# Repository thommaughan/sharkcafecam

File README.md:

# sharkcafecam
SharkCafe Cam - white shark camera tag with behavior detection triggered video

### How to navigate this repository
First of all, welcome to Shark Cafe Camera. The first thing that you will need to review is the "ToolList.md" file. This will provide you with the necessary tools and optional tools that will assist you with completing this project. Each tool is listed as the name of the tool, cost, and a blue hyperlink text which will take you the the website to order that tool. Tools that are listed as optional are not necessary for the project but can provide some ease with certain aspects. The tools listed as none optional were chosen as ideal due to the fact that you can go to your local hardware store and purchase these tools and they are the relatively cheaper versions. These are not the specific tools we used for this project but are merely recommendations. Feel free to find, borrow, or use other tools that will accomplish the same tasks.

The next step if you are not familiar with soldering should be to review the "SolderingBasics.md". This will provide you a brief overview of soldering tools and techniques that will assist you with this project. Feel free to also research other resources for example you tube videos or manuals as these can provide more detailed information about this topic.

After you have completed the first two sections or you are familiar with soldering then you are ready to navigation the rest of this repository. The organization of this reprository is as follows. Each folder describes a certain component of the overall project. The subfolders within each of these folders has  a combination of subfolder including a readme.md, mechanical, electrical, and software. First, you should open the "readme.md" which provides necessary information or steps for that component. The Mechanical describes any physical component or mechanism for that component. The electrical describes the components used and how the were wired. The software describes any software that was used to control the electrical components. 

Use these materials as guidelines to further experiment with other cameras or devices. This is merely to show how this project was accomplished and the potential possibilities. 

If you have any questions or any part of these materials are confusion, please feel free to leave comments on sections that are confusing. 

Have fun and go exploring with your new remote sensing camera!

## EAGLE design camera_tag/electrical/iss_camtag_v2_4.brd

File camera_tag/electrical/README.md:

# Shark Cafe Cam Main Board Information
## Files
#### 1. Schematic
#### 2. Board design
## Internal components

#### 1. Processor
#### 2. Sensors  
   Note: We show breakout boards for the sensors to show that these can be bought seperately, utilized individually, and have code and tutrials available by their manufacturers online. On the board these sensors are cut down to the essentials to make for a more compact design.
#### 3. Camera trigger
```
Note on camera trigger transistors: they allow for switching the camera on/off and record/stop. These transistors work by allowing current to flow through the camera when they are triggered. In a way they act as an electrical switch, when power is sent to them you're flipping the switch 'on', thus activating the camera, when no power is sent, the switch is flipped 'off' and the camera disactivates.
```

### Processor

| Part         | Function          | Board Code    | Description       | Link and part number      |
| --------------------|:-------------:|:-------------:|-----------------|----------------- |
|  | Processor | N/A | Central processing. Same processor found in Feather M0, can be accessed as such through Arduino IDE.| ATSAMD21G18A |

### Sensors (included)

| Part breakout board         | Function          | Board Code    | Description       | Link and part number      |
| --------------------|:-------------:|:-------------:|-----------------|:---------------------------:|
|   | RGB sensor  | U1  | Red, green, blue light sensor  |  [ISL29125](https://www.sparkfun.com/products/12829)   |
|   | IMU        | U4           | Accelerometer, gyroscope, and compass | [MPU-9250](https://www.invensense.com/products/motion-tracking/9-axis/mpu-9250/)   |
|   | Capacitive sensing         |   U6   | 4 Channel Capacitance to Digital Converter  | [FDC1004](http://www.ti.com/product/FDC1004)  |

### Trigger (for camera or other device. Transistor.)

| Location on board         | Function          | Board Code    | Description       | Link and part number      |
| --------------------|:-------------:| -------------|-----------------|---------------------------|
|   |  2 FETs, one turns the camera on/off and the other records/stops.  | CAM1  | Trigger for camera. R and P are transistor drains, G is the common source.  |  [Transistors](https://learn.sparkfun.com/tutorials/transistors/all#extending-the-water-analogy)   |

### Electrical components

| Part Number/Name         | Function          | Board Code    | Description       | Link       |
|:--------------------:|:-------------:|:-------------:|:-----------------:|:-----------------:|
| SN74LVC2G66DCUR  | Switch         | U5    | Dual Bilateral Analog Switch  | [SN74LVC2G66DCUR](http://www.ti.com/lit/ds/symlink/sn74lvc2g66.pdf)  |
| TPS22918            | Load Switch         | U8     | Details in datasheet  | [TPS22918](http://www.ti.com/product/TPS22918)  |
| 2N7002BKS           | MOSFET         | Q1     | Transistor drain  | [2N7002BKS](https://assets.nexperia.com/documents/data-sheet/2N7002BKS.pdf)  |
| ZXCT1109            | Current sense monitor         |   U9   | Details in datasheet  | [ZXCT1109](https://www.diodes.com/assets/Datasheets/ZXCT1107_10.pdf)  |
| TPS78033            | LDO regulator         | U7     | Details in datasheet  | [TPS78033](https://www.findchips.com/detail/tps78033/2477-Texas%20Instruments?quantity=1)  |
| MCP73831            | Charge Management controller         |  U3    | Details in datasheet  | [MCP73831](https://cdn.sparkfun.com/assets/learn_tutorials/6/9/5/MCP738312.pdf)  |
| Direct wire uSD connect        | Micro SD card connector         |   J9   | Pins for soldering MicroSD card on.  | N/A  |
| USB-MICROB 5v                | Data transfer and power with computer         | J6     | Micro USB connector port  | N/A  |
   
 ### *For information on how to communicate with the board and each sensor, check out the software section.*

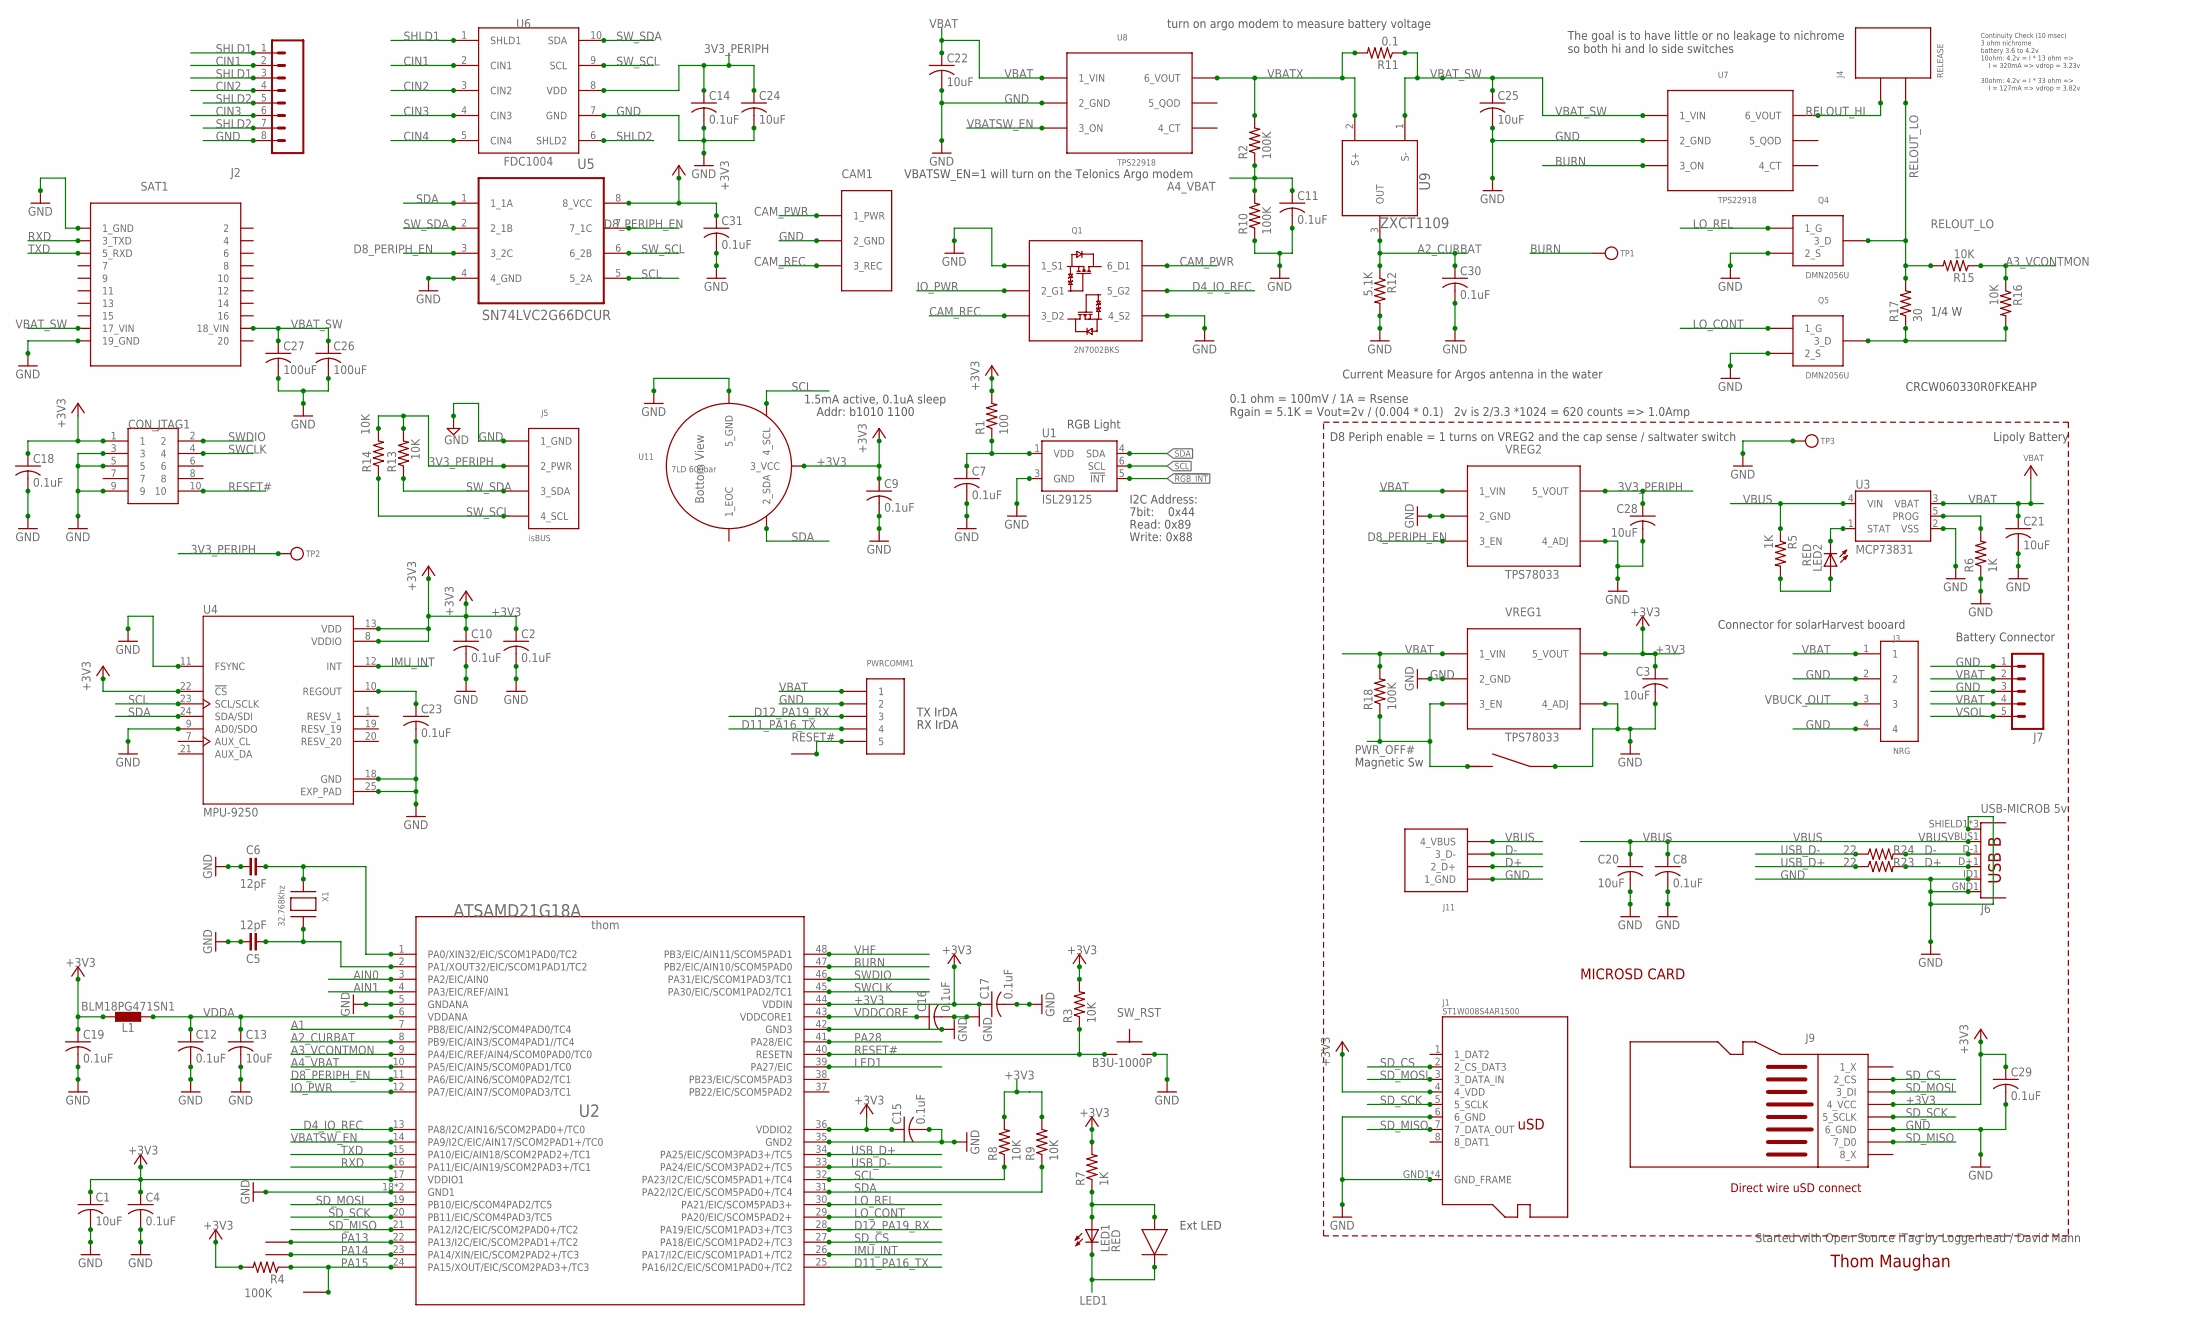
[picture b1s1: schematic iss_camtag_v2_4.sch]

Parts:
C1, C13, C20, C21, C22, C24, C25: 10uF; C0603
C2, C4, C7, C8, C9, C10, C11, C12, C14, C15, C16, C17, C18, C19, C23, C29, C30, C31: 0.1uF; C0402
C3, C28: 10uF; C0603K
C5, C6: 12pF; C0402
C26, C27: 100uF; C1210
CAM1: CON_1X3_CAMCTRL
CON_JTAG1: HDR-SMT-50MIL/5X2
J1: ST1W008S4AR1500; MICROSD_JAE_ST1W008S4AR1500
J2: CONN_08"; 1X08
J3: NRG; CONNECTOR_1X4_0_1
J4: RELEASE; CON_1X2_0_1
J5: isBUS; CON_1X4_0_1
J6: USB-MICROB 5v; USB-B-MICRO-SMD_V03
J7: M05PTH; 1X05
J9: CON_8_MICROSD_WIRE
J11: CON_1X4_2MM_THRU
L1: BLM18PG471SN1; C0603
LED1, LED2: RED; CHIPLED_0603
PWRCOMM1: CON_1X5_0_1; CONNECTOR_1X5_0_1
Q1: 2N7002BKS; SOT363
Q4, Q5: DMN2056U; SOT23-3
R1: 100; R0402
R2, R4, R10, R18: 100K; R0402
R3, R8, R9, R13, R14, R15, R16: 10K; R0402
R5, R6, R7: 1K; R0402
R11: 0.1; R0603
R12: 5.1K; R0402
R17: 30; R0603
R23, R24: 22; R0402
SAT1: TELONICS-ST-21H2-200A; TELONICS_ST_21H2-200A
SW_RST: B3U-1000P
TP1, TP2, TP3: TESTPOINTROUND1.5MM; TESTPOINT_ROUND_1.5MM
TP4, TP5, TP6: CON_1
U1: ISL29125; ODFN-LD-6
U2: ATSAMD21G18A; TQFN48_7MM
U3: MCP73831; SOT23-5
U4: MPU-9250; MPU-9250-FOOTPRINT
U5: SN74LVC2G66DCUR; ANALOG_SW_SN74LVCG66DCUR
U6: FDC1004; VSSOP-10
U7, U8: TPS22918; SOT23-6
U9: ZXCT1109; SOT23
U11: 7LD 600bar; KELLER_7LD
U$3: CON_2_MAGSW
U$4: CON_2_LED
U$5: CON_1
VREG1, VREG2: TPS78033; SOT23-5
X1: 32.768Khz; XTAL_ABS06

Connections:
3V3_PERIPH: C14.1, C24.1, C28.1, J5.P$2 (2_PWR), R13.2, R14.2, TP2.P$1, U6.8 (VDD), VREG2.P$5 (5_VOUT)
!RGB_INT: U1.5 (!INT)
+3V3: C1.1, C2.1, C3.1, C4.1, C9.1, C10.1, C15.1, C17.1, C18.1, C19.1, C29.1, C31.1, CON_JTAG1.1, J1.4 (4_VDD), J9.4_VCC, J9.P4 (4_VCC), L1.2, R1.2, R3.2, R4.2, R7.2, R8.2, R9.2, U2.17 (VDDIO1), U2.36 (VDDIO2), U2.44 (VDDIN), U4.8 (VDDIO), U4.13 (VDD), U4.22 (!CS), U5.8 (8_VCC), U11.3_VCC, VREG1.P$5 (5_VOUT)
A1: U2.7 (PB8/EIC/AIN2/SCOM4PAD0/TC4)
A2_CURBAT: C30.1, R12.1, U2.8 (PB9/EIC/AIN3/SCOM4PAD1//TC4), U9.3 (OUT)
A3_VCONTMON: R15.1, R16.1, U2.9 (PA4/EIC/REF/AIN4/SCOM0PAD0/TC0)
A4_VBAT: C11.1, R2.1, R10.2, U2.10 (PA5/EIC/AIN5/SCOM0PAD1/TC0)
AIN0: U2.3 (PA2/EIC/AIN0)
AIN1: U2.4 (PA3/EIC/REF/AIN1)
BURN: TP1.P$1, U2.47 (PB2/EIC/AIN10/SCOM5PAD0), U7.3 (3_ON)
CAM_PWR: CAM1.1_PWR, Q1.6 (6_D1)
CAM_REC: CAM1.3_REC, Q1.3 (3_D2)
CIN1: J2.2, U6.2 (CIN1)
CIN2: J2.4, U6.3 (CIN2)
CIN3: J2.6, U6.4 (CIN3)
CIN4: U6.5 (CIN4)
D4_IO_REC: Q1.5 (5_G2), U2.13 (PA8/I2C/AIN16/SCOM2PAD0+/TC0)
D8_PERIPH_EN: U2.11 (PA6/EIC/AIN6/SCOM0PAD2/TC1), U5.3 (3_2C), U5.7 (7_1C), VREG2.P$3 (3_EN)
D11_PA16_TX: PWRCOMM1.4, U2.25 (PA16/I2C/EIC/SCOM1PAD0+/TC2)
D12_PA19_RX: PWRCOMM1.3, U2.28 (PA19/EIC/SCOM1PAD3+/TC3)
D+: J6.D+1 (D+), J11.P$2 (2_D+), R23.2
D-: J6.D-1 (D-), J11.P$3 (3_D-), R24.2
GND: C1.2, C2.2, C3.2, C4.2, C5.2, C6.1, C7.2, C8.2, C9.2, C10.2, C11.2, C12.2, C13.2, C14.2, C15.2, C16.2, C17.2, C18.2, C19.2, C20.2, C21.2, C22.2, C23.2, C24.2, C25.2, C26.2, C27.2, C28.2, C29.2, C30.2, C31.2, CAM1.2_GND, CON_JTAG1.3, CON_JTAG1.5, CON_JTAG1.9, J1.6 (6_GND), J1.GND1 (GND_FRAME), J1.GND2 (GND_FRAME), J1.GND3 (GND_FRAME), J1.GND4 (GND_FRAME), J2.8, J3.2, J3.4, J5.P$1 (1_GND), J6.GND1 (GND), J6.ID1 (USBID), J6.SHIELD1 (SHIELD), J6.SHIELD2 (SHIELD), J6.SHIELD3 (SHIELD), J7.1, J7.3, J9.6_GND, J9.P6 (6_GND), J11.P$1 (1_GND), PWRCOMM1.2, Q1.1 (1_S1), Q1.4 (4_S2), Q4.2 (2_S), Q5.2 (2_S), R6.1, R10.1, R12.2, SAT1.1 (1_GND), SAT1.19 (19_GND), SAT1.21 (1_GND), SAT1.39 (19_GND), SW_RST.P$2, TP3.P$1, U1.3 (GND), U2.5 (GNDANA), U2.18 (GND1), U2.35 (GND2), U2.42 (GND3), U2.THERMAL (GND1), U3.2 (VSS), U4.9 (AD0/SDO), U4.11 (FSYNC), U4.18 (GND), U4.25 (EXP_PAD), U5.4 (4_GND), U6.7 (GND), U7.2 (2_GND), U8.2 (2_GND), U11.5_GND, U$3.2, VREG1.P$2 (2_GND), VREG1.P$4 (4_ADJ), VREG2.P$2 (2_GND), VREG2.P$4 (4_ADJ)
IMU_INT: U2.26 (PA17/I2C/EIC/SCOM1PAD1+/TC2), U4.12 (INT)
IO_PWR: Q1.2 (2_G1), U2.12 (PA7/EIC/AIN7/SCOM0PAD3/TC1)
LAN: LED1.A, R7.1, U$4.P$1 (1A)
LED1: LED1.C, U2.39 (PA27/EIC), U$4.P$2 (2K)
LO_CONT: Q5.1 (1_G), U2.29 (PA20/EIC/SCOM5PAD2+)
LO_REL: Q4.1 (1_G), U2.30 (PA21/EIC/SCOM5PAD3+)
unnamed: C6.2, U2.1 (PA0/XIN32/EIC/SCOM1PAD0/TC2), X1.P$1
unnamed: LED2.C, U3.1 (STAT)
unnamed: LED2.A, R5.2
unnamed: R6.2, U3.5 (PROG)
unnamed: C7.1, R1.1, U1.1 (VDD)
unnamed: C5.1, U2.2 (PA1/XOUT32/EIC/SCOM1PAD1/TC2), X1.P$2
unnamed: Q5.3 (3_D), R16.2, R17.1
unnamed: C23.1, U4.10 (REGOUT)
PA13: TP4.P$1, U2.22 (PA13/I2C/EIC/SCOM2PAD1+/TC2)
PA14: TP5.P$1, U2.23 (PA14/XIN/EIC/SCOM2PAD2+/TC3)
PA15: R4.1, TP6.P$1, U2.24 (PA15/XOUT/EIC/SCOM2PAD3+/TC3)
PA28: U2.41 (PA28/EIC)
PWR_OFF#: R18.1, U$3.1, VREG1.P$3 (3_EN)
RELOUT_HI: J4.P$1, U7.6 (6_VOUT)
RELOUT_LO: J4.P$2, Q4.3 (3_D), R15.2, R17.2
RESET#: CON_JTAG1.10, PWRCOMM1.5, R3.1, SW_RST.P$1, U2.40 (RESETN), U$5.P$1
RXD: SAT1.3 (3_TXD), SAT1.23 (3_TXD), U2.16 (PA11/EIC/AIN19/SCOM2PAD3+/TC1)
SCL: R8.1, U1.6 (SCL), U2.32 (PA23/I2C/EIC/SCOM5PAD1+/TC4), U4.23 (SCL/SCLK), U5.5 (5_2A), U11.4_SCL
SDA: R9.1, U1.4 (SDA), U2.31 (PA22/I2C/EIC/SCOM5PAD0+/TC4), U4.24 (SDA/SDI), U5.1 (1_1A), U11.2_SDA
SD_CS: J1.2 (2_CS_DAT3), J9.2_CS, J9.P2 (2_CS), U2.27 (PA18/EIC/SCOM1PAD2+/TC3)
SD_MISO: J1.7 (7_DATA_OUT), J9.7_DO (7_D0), J9.P7 (7_D0), U2.21 (PA12/I2C/EIC/SCOM2PAD0+/TC2)
SD_MOSI: J1.3 (3_DATA_IN), J9.3_DI, J9.P3 (3_DI), U2.19 (PB10/EIC/SCOM4PAD2/TC5)
SD_SCK: J1.5 (5_SCLK), J9.5_SCK (5_SCLK), J9.P5 (5_SCLK), U2.20 (PB11/EIC/SCOM4PAD3/TC5)
SHLD1: J2.1, J2.3, U6.1 (SHLD1)
SHLD2: J2.5, J2.7, U6.6 (SHLD2)
SWCLK: CON_JTAG1.4, U2.45 (PA30/EIC/SCOM1PAD2/TC1)
SWDIO: CON_JTAG1.2, U2.46 (PA31/EIC/SCOM1PAD3/TC1)
SW_SCL: J5.P$4 (4_SCL), R14.1, U5.6 (6_2B), U6.9 (SCL)
SW_SDA: J5.P$3 (3_SDA), R13.1, U5.2 (2_1B), U6.10 (SDA)
TXD: SAT1.5 (5_RXD), SAT1.25 (5_RXD), U2.15 (PA10/EIC/AIN18/SCOM2PAD2+/TC1)
USB_D+: R23.1, U2.34 (PA25/EIC/SCOM3PAD3+/TC5)
USB_D-: R24.1, U2.33 (PA24/EIC/SCOM3PAD2+/TC5)
VBAT: C21.1, C22.1, J3.1, J7.2, J7.4, PWRCOMM1.1, R18.2, U3.3 (VBAT), U8.1 (1_VIN), VREG1.P$1 (1_VIN), VREG2.P$1 (1_VIN)
VBATSW_EN: U2.14 (PA9/I2C/EIC/AIN17/SCOM2PAD1+/TC0), U8.3 (3_ON)
VBATX: R2.2, R11.2, U8.6 (6_VOUT), U9.2 (S+)
VBAT_SW: C25.1, C26.1, C27.1, R11.1, SAT1.17 (17_VIN), SAT1.18 (18_VIN), SAT1.37 (17_VIN), SAT1.38 (18_VIN), U7.1 (1_VIN), U9.1 (S-)
VBUCK_OUT: J3.3
VBUS: C8.1, C20.1, J6.VBUS1 (VBUS), J11.P$4 (4_VBUS), R5.1, U3.4 (VIN)
VDDA: C12.1, C13.1, L1.1, U2.6 (VDDANA)
VDDCORE: C16.1, U2.43 (VDDCORE1)
VHF: U2.48 (PB3/EIC/AIN11/SCOM5PAD1)
VSOL: J7.5

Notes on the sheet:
MICROSD CARD
7bit: 0x44
I2C Address:
Read: 0x89
Write: 0x88
Addr: b1010 1100
Lipoly Battery
RGB Light
turn on argo modem to measure battery voltage
Continuity Check (10 msec) 3 ohm nichrome battery 3.6 to 4.2v 10ohm: 4.2v = I * 13 ohm => I = 320mA => vdrop = 3.23v 30ohm: 4.2v = I * 33 ohm => I = 127mA => vdrop = 3.82v
The goal is to have little or no leakage to nichrome so both hi and lo side switches
CRCW060330R0FKEAHP
1/4 W
1.5mA active, 0.1uA sleep
Connector for solarHarvest booard
Battery Connector
Thom Maughan
Direct wire uSD connect
VBATSW_EN=1 will turn on the Telonics Argo modem
Magnetic Sw
0.1 ohm = 100mV / 1A = Rsense Rgain = 5.1K = Vout=2v / (0.004 * 0.1) 2v is 2/3.3 *1024 = 620 counts => 1.0Amp
Started with Open Source iTag by Loggerhead / David Mann
Current Measure for Argos antenna in the water
D8 Periph enable = 1 turns on VREG2 and the cap sense / saltwater switch
TX IrDA
RX IrDA
Ext LED

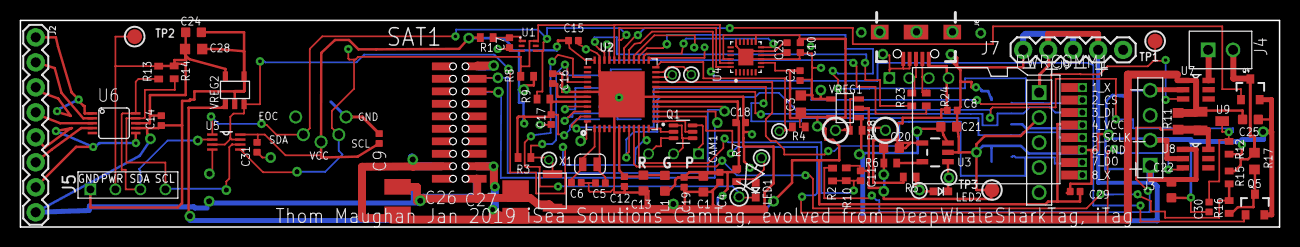
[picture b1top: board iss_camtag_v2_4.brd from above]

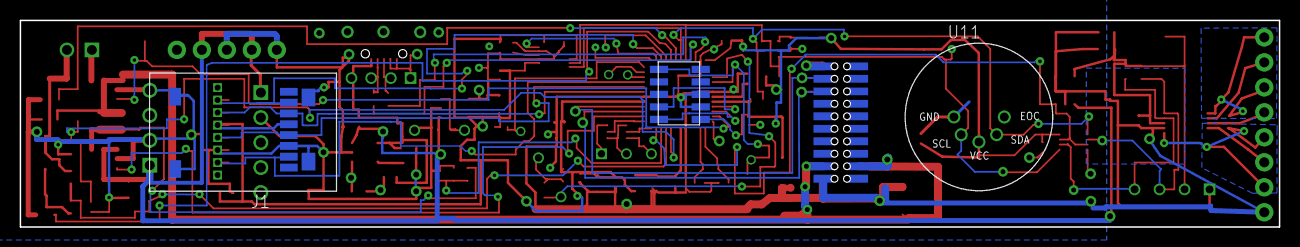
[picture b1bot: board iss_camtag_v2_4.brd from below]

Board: 4 copper layers, 128.0 x 21.0 mm, 93 parts (3 on the bottom side), 62 nets.

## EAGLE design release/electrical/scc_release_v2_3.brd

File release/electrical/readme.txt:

Readme.txt
[1-7ReleaseBoard.pdf](https://github.com/practicaltech/TechFest/files/3468464/1-7ReleaseBoard.pdf)

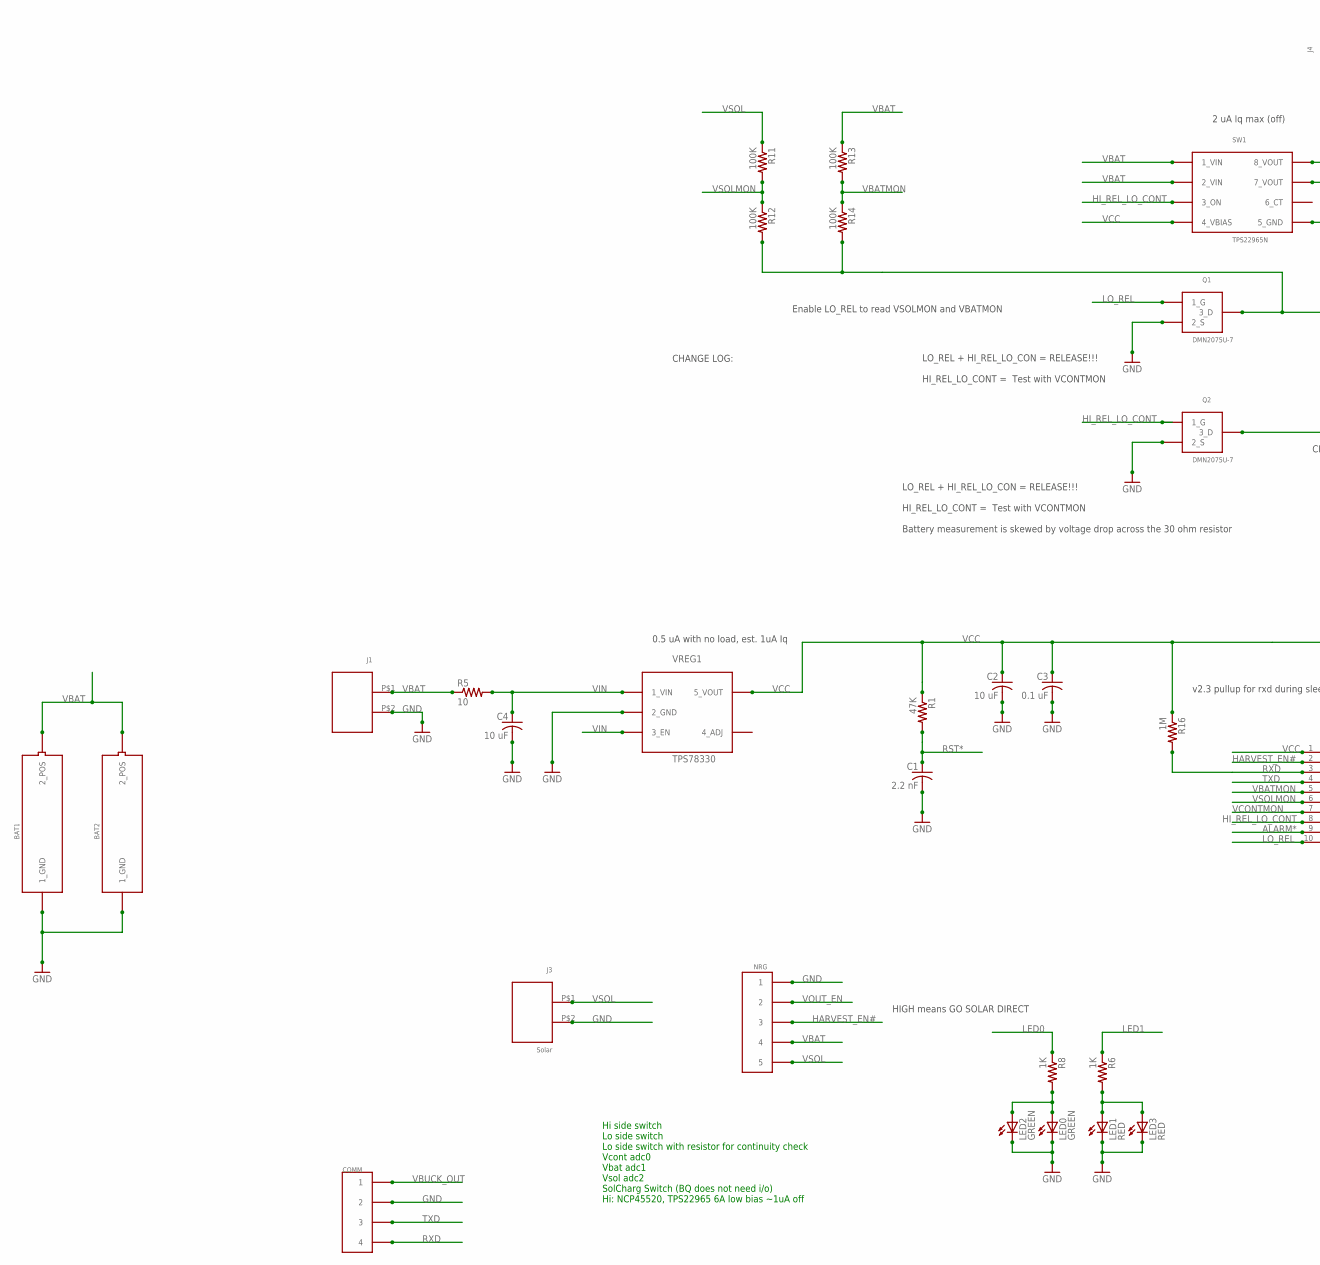
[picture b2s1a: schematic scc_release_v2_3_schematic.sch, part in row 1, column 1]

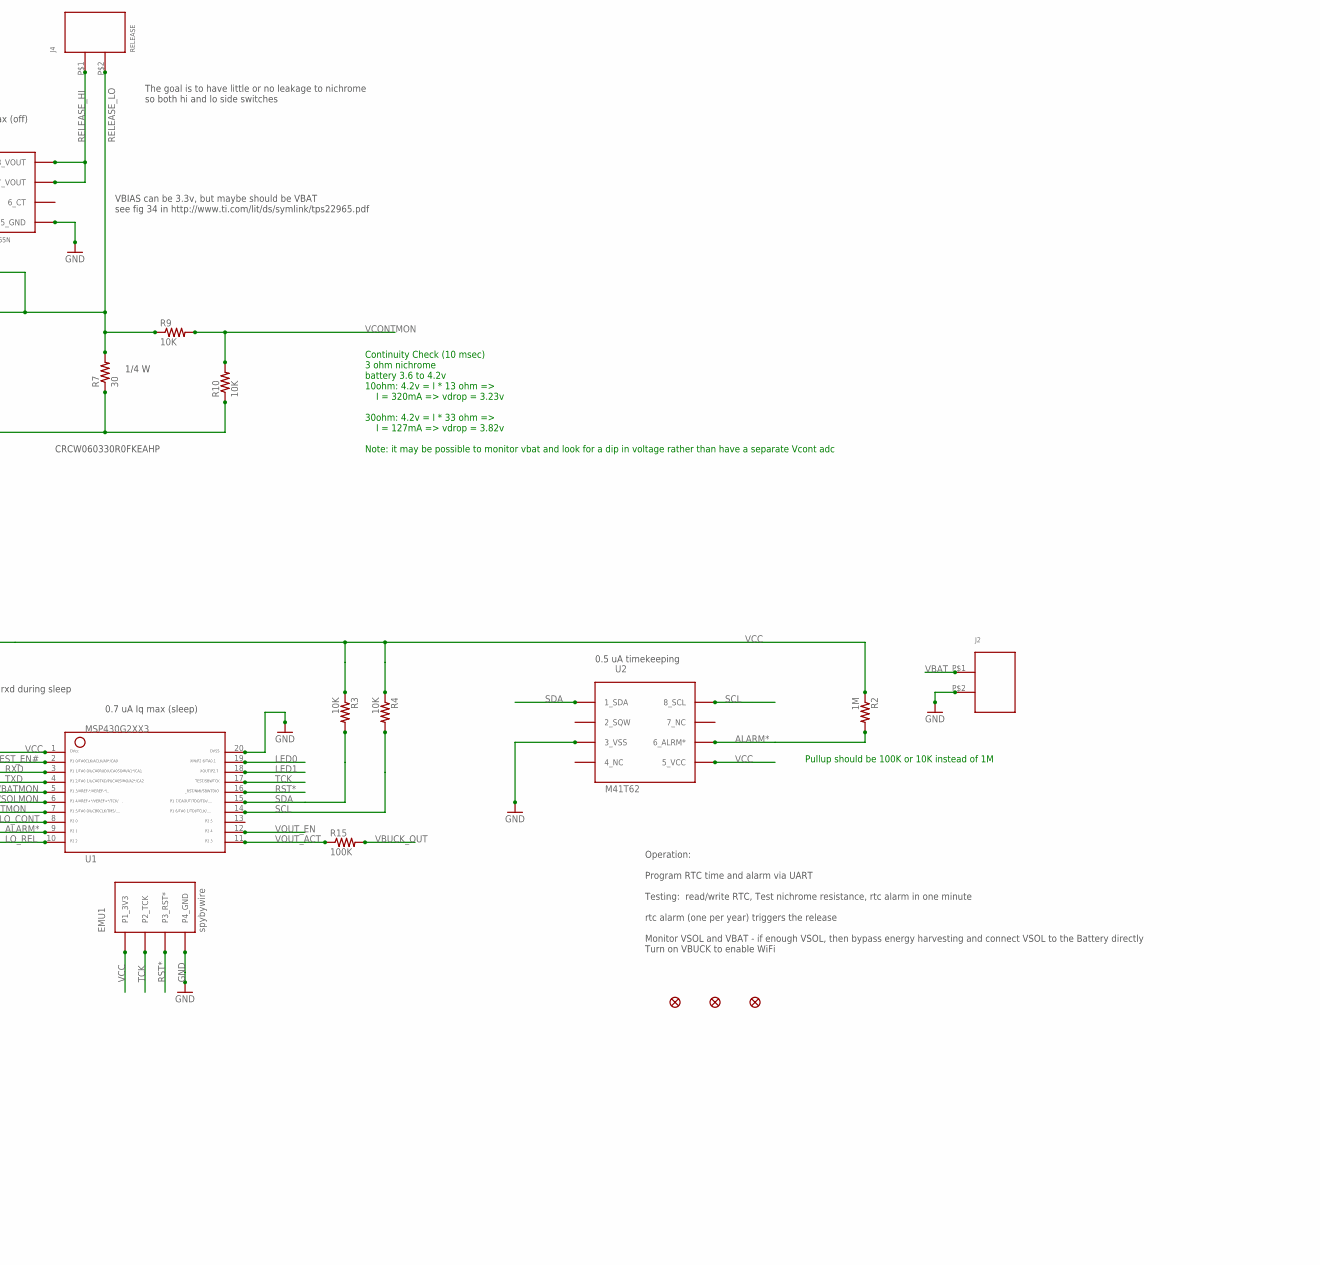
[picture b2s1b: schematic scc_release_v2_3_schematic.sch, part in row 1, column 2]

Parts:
BAT1, BAT2: BAT_10440
C1: 2.2 nF; C0603K
C2, C4: 10 uF; C0603K
C3: 0.1 uF; C0603K
COMM: CON_1X4_050
EMU1: spybywire; EMU_MSP_SPYBYWIRE_4_050
J1, J2: CON_1X2_0_1
J3: Solar; CON_1X2_0_1
J4: RELEASE; CON_1X2_0_1
JP1, JP2, JP3: FIDUCIAL1.5X3; FIDUCIAL-1.5X3
LED0, LED2: GREEN; CHIPLED_0805
LED1, LED3: RED; CHIPLED_0805
NRG: CON_1X5_050
Q1, Q2: DMN2075U-7; SOT23-3
R1: 47K; R0603
R2, R16: 1M; R0603
R3, R4, R9, R10: 10K; R0603
R5: 10; R0603
R6, R8: 1K; R0603
R7: 30; R0603
R11, R12, R13, R14, R15: 100K; R0603
SW1: TPS22965N; TI_WSON8
U1: MSP430G2553; PW20
U2: M41T62; M41T62_PKG
VREG1: TPS78330; SOT23-5

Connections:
ALARM*: R2.2, U1.9, U2.P$6 (6_ALRM*)
GND: BAT1.P$1 (1_GND), BAT2.P$1 (1_GND), C1.2, C2.2, C3.2, C4.2, COMM.P$2 (2), COMM.P$6 (2), COMM.P$10 (2), EMU1.P4_GND, J1.P$2, J2.P$2, J3.P$2, LED0.C, LED1.C, LED2.C, LED3.C, NRG.P$1 (1), NRG.P$6 (1), NRG.P$11 (1), Q1.2 (2_S), Q2.2 (2_S), SW1.P$5 (5_GND), SW1.P$9 (5_GND), U1.20, U2.P$3 (3_VSS), VREG1.P$2 (2_GND)
HARVEST_EN#: NRG.P$3 (3), NRG.P$8 (3), NRG.P$13 (3), U1.2
HI_REL_LO_CONT: Q2.1 (1_G), SW1.P$3 (3_ON), U1.8
LED0: R8.1, U1.19
LED1: R6.1, U1.18
LO_REL: Q1.1 (1_G), U1.10
unnamed: LED1.A, LED3.A, R6.2
unnamed: Q2.3 (3_D), R7.1, R10.1
unnamed: LED0.A, LED2.A, R8.2
RELEASE_HI: J4.P$1, SW1.P$7 (7_VOUT), SW1.P$8 (8_VOUT)
RELEASE_LO: J4.P$2, Q1.3 (3_D), R7.2, R9.1, R12.2, R14.2
RST*: C1.1, EMU1.P3_RST*, R1.2, U1.16
RXD: COMM.P$4 (4), COMM.P$8 (4), COMM.P$12 (4), R16.2, U1.3
SCL: R4.2, U1.14, U2.P$8 (8_SCL)
SDA: R3.2, U1.15, U2.P$1 (1_SDA)
TCK: EMU1.P2_TST (P2_TCK), U1.17
TXD: COMM.P$3 (3), COMM.P$7 (3), COMM.P$11 (3), U1.4
VBAT: BAT1.P$2 (2_POS), BAT2.P$2 (2_POS), J1.P$1, J2.P$1, NRG.P$4 (4), NRG.P$9 (4), NRG.P$14 (4), R5.1, R13.1, SW1.P$1 (1_VIN), SW1.P$2 (2_VIN)
VBATMON: R13.2, R14.1, U1.5
VBUCK_OUT: COMM.P$1 (1), COMM.P$5 (1), COMM.P$9 (1), R15.2
VCC: C2.1, C3.1, EMU1.P1_3V3, R1.1, R2.1, R3.1, R4.1, R16.1, SW1.P$4 (4_VBIAS), U1.1, U2.P$5 (5_VCC), VREG1.P$5 (5_VOUT)
VCONTMON: R9.2, R10.2, U1.7
VIN: C4.1, R5.2, VREG1.P$1 (1_VIN), VREG1.P$3 (3_EN)
VOUT_ACT: R15.1, U1.11
VOUT_EN: NRG.P$2 (2), NRG.P$7 (2), NRG.P$12 (2), U1.12
VSOL: J3.P$1, NRG.P$5 (5), NRG.P$10 (5), NRG.P$15 (5), R11.1
VSOLMON: R11.2, R12.1, U1.6

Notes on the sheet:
Hi side switch Lo side switch Lo side switch with resistor for continuity check Vcont adc0 Vbat adc1 Vsol adc2 SolCharg Switch (BQ does not need i/o) Hi: NCP45520, TPS22965 6A low bias ~1uA off
Continuity Check (10 msec) 3 ohm nichrome battery 3.6 to 4.2v 10ohm: 4.2v = I * 13 ohm => I = 320mA => vdrop = 3.23v 30ohm: 4.2v = I * 33 ohm => I = 127mA => vdrop = 3.82v Note: it may be possible to monitor vbat and look for a dip in voltage rather than have a separate Vcont adc
The goal is to have little or no leakage to nichrome so both hi and lo side switches
CRCW060330R0FKEAHP
1/4 W
LO_REL + HI_REL_LO_CON = RELEASE!!! HI_REL_LO_CONT = Test with VCONTMON
HIGH means GO SOLAR DIRECT
Operation: Program RTC time and alarm via UART Testing: read/write RTC, Test nichrome resistance, rtc alarm in one minute rtc alarm (one per year) triggers the release Monitor VSOL and VBAT - if enough VSOL, then bypass energy harvesting and connect VSOL to the Battery directly Turn on VBUCK to ena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
2 uA Iq max (off)
0.7 uA Iq max (sleep)
0.5 uA timekeeping
0.5 uA with no load, est. 1uA Iq
Enable LO_REL to read VSOLMON and VBATMON
CHANGE LOG:
VBIAS can be 3.3v, but maybe should be VBAT see fig 34 in http://www.ti.com/lit/ds/symlink/tps22965.pdf
LO_REL + HI_REL_LO_CON = RELEASE!!! HI_REL_LO_CONT = Test with VCONTMON Battery measurement is skewed by voltage drop across the 30 ohm resistor
v2.3 pullup for rxd during sleep
Pullup should be 100K or 10K instead of 1M

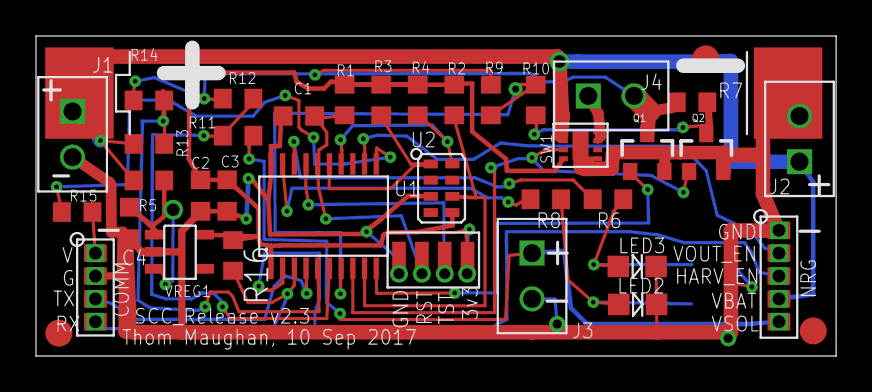
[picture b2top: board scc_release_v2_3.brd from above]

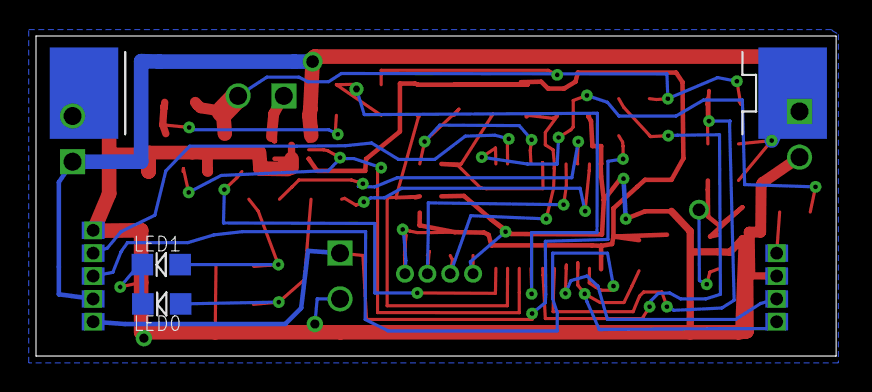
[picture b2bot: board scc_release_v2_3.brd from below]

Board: 2 copper layers, 44.5 x 17.8 mm, 42 parts (3 on the bottom side), 28 nets.

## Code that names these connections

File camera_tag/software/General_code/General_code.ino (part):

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#define BOARDTYPE 1   // 0 means Feather M0, 1 means thomz dwsTag

#if BOARDTYPE == 1
#define LED1            26      //26 //PA27  { PORTA, 27, PIO_TIMER, PIN_ATTR_DIGITAL, No_ADC_Channel, NOT_ON_PWM, NOT_ON_TIMER, EXTERNAL_INT_15 }, // p39 previously TX LED
#define D10_SD_CS       10      //10 //PA18 { PORTA, 18, PIO_TIMER, (PIN_ATTR_DIGITAL|PIN_ATTR_PWM|PIN_ATTR_TIMER), No_ADC_Channel, PWM3_CH0, TC3_CH0, EXTERNAL_INT_2 }, // p27
#define A2_CURBAT       16      //16 //PB9 { PORTB,  9, PIO_ANALOG, (PIN_ATTR_PWM|PIN_ATTR_TIMER), ADC_Channel3, PWM4_CH1, TC4_CH1, EXTERNAL_INT_9 }, // p8
#define A4_VBAT         18      //18 //PA5 { PORTA,  5, PIO_ANALOG, (PIN_ATTR_PWM|PIN_ATTR_TIMER), ADC_Channel5, PWM0_CH1, TCC0_CH1, EXTERNAL_INT_5 }, // p10
#define D8_PERIPH_VREG_EN  8     //8  //PA6  { PORTA,  6, PIO_ANALOG, (PIN_ATTR_PWM|PIN_ATTR_TIMER), ADC_Channel6, PWM1_CH0, TCC1_CH0, EXTERNAL_INT_6 }, // p11
#define D9_IO_PWR       9       //9  //PA7  { PORTA,  7, PIO_ANALOG, (PIN_ATTR_PWM|PIN_ATTR_TIMER), ADC_Channel7, PWM1_CH1, TCC1_CH1, EXTERNAL_INT_7 }, // p12
#define D4_IO_REC       4       //4 //PA8  { PORTA,  8, PIO_TIMER, (PIN_ATTR_DIGITAL|PIN_ATTR_PWM|PIN_ATTR_TIMER), ADC_Channel16, PWM0_CH0, TCC0_CH0, EXTERNAL_INT_NMI }, // p23
#define VBATSW_EN       3       //3  //PA9  { PORTA,  9, PIO_TIMER, (PIN_ATTR_DIGITAL|PIN_ATTR_PWM|PIN_ATTR_TIMER), ADC_Channel17, PWM0_CH1, TCC0_CH1, EXTERNAL_INT_9 }, // p14
#define LO_CONT         6       //6  //PA20 { PORTA, 20, PIO_TIMER_ALT, (PIN_ATTR_DIGITAL|PIN_ATTR_PWM|PIN_ATTR_TIMER_ALT), No_ADC_Channel, PWM0_CH6, TCC0_CH6, EXTERNAL_INT_4 }, // p29
#define LO_REL          7       //7  //PA21 { PORTA, 21, PIO_TIMER_ALT, (PIN_ATTR_DIGITAL|PIN_ATTR_PWM|PIN_ATTR_TIMER_ALT), No_ADC_Channel, PWM0_CH7, TCC0_CH7, EXTERNAL_INT_5 }, // p30
#define HI_REL          19      //19 //PB2 { PORTB,  2, PIO_ANALOG, 0, ADC_Channel10, NOT_ON_PWM, NOT_ON_TIMER, EXTERNAL_INT_2 }, // p47
#define D13_IMU_INT     13      //13 //PA17 { PORTA, 17, PIO_TIMER, (PIN_ATTR_DIGITAL|PIN_ATTR_PWM|PIN_ATTR_TIMER), No_ADC_Channel, PWM2_CH1, TCC2_CH1, EXTERNAL_INT_1 }, // p26 SCK
#define VCONTMON        17      //V1.8 hardware not routed, 17 //PA4 { PORTA,  4, PIO_ANALOG, (PIN_ATTR_PWM|PIN_ATTR_TIMER), ADC_Channel4, PWM0_CH0, TCC0_CH0, EXTERNAL_INT_4 }, // p9
#define SERCOM1_RX      12      // atsamd21g sercom1 peripheral is mapped to software Serial2 object
#define SERCOM1_TX      11      // atsamd21g sercom1 peripheral

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
//RGB
SFE_ISL29125 RGB_sensor;//RGB sensor 
#define LEDRED      LED1
#define SD_CS       D10_SD_CS
#endif
//-------------------------------

File logfile;

// RX on pin 12 which is portA on the processor PA19, TX on pin 11 PA16
Uart Serial2 (&sercom1, SERCOM1_RX, SERCOM1_TX, SERCOM_RX_PAD_3, UART_TX_PAD_0);

void setup()
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
  
#if BOARDTYPE == 1  
    pinMode(D8_PERIPH_VREG_EN, OUTPUT);     //8  //PA6
    digitalWrite(D8_PERIPH_VREG_EN, HIGH);   // voltage regulator for FCD1004 (if left off, causes i2c hang)
    pinMode(VBATSW_EN, OUTPUT);             //3  //PA9
    digitalWrite(VBATSW_EN, LOW);
    pinMode(LED1, OUTPUT);            //26 //PA27// appLed (was ledGreen on iTag, is redLed on dwstag)
    digitalWrite(LED1, LOW);
    pinMode(LO_CONT, OUTPUT);        //6  //PA20  // LO_CONT PA20
    digitalWrite(LO_CONT, LOW);  
    pinMode(LO_REL, OUTPUT);          //7  //PA21
    digitalWrite(LO_REL, LOW);       // LO_REL PA21
    pinMode(HI_REL, OUTPUT);          //19 //PB2
    digitalWrite(HI_REL, LOW);        // aka BURN (burn is used on schematic for iTag compat)

    //new
    pinMode(D10_SD_CS, OUTPUT);     //10 //PA18// used for sd card
    digitalWrite(D10_SD_CS, LOW);
    pinMode(D9_IO_PWR, OUTPUT);   //9  //PA7
    digitalWrite(D9_IO_PWR, LOW);
    pinMode(D4_IO_REC, OUTPUT);          //4 //PA8
    digitalWrite(D4_IO_REC, LOW);

    pinMode(D13_IMU_INT, INPUT);      //13 //PA17   Not used?? 
        
    // PB9, pin 8, A2 is CURBAT  BatteryCurrent
    pinMode(A2_CURBAT, INPUT);
    pinMode(A4_VBAT, INPUT);  
    pinMode(VCONTMON, INPUT);    // A3 //PA4
    pinMode(A4_VBAT, INPUT);        //18 //PA5

     //Test RGB initialization
      if (RGB_sensor.init()){
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  digitalWrite(LED1, HIGH);
  //delay(100);
  //digitalWrite(D9_IO_PWR, HIGH);*********************
  digitalWrite(D4_IO_REC, HIGH);    // This pin might have an issue with uSD
  for(int indx = 0; indx< 5; indx++)
  {
// GABE: look for activity on D4_IO_REC during this loop and the one below - if there is
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
  digitalWrite(LED1, LOW);  
  //digitalWrite(D9_IO_PWR, LOW);******************************
  digitalWrite(D4_IO_REC, LOW);    // This pin might have an issue with uSD
  for(int indx = 0; indx< 5; indx++)
  {
    logfile.print("A0 = "); logfile.println(analogRead(0));
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
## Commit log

2019-07-09 Create fuck
2019-07-09 Added software source files for MSP430 Release Controller
2019-07-09 GitBook: [master] 2 pages modified
2019-07-09 GitBook: [master] one page modified
2019-07-09 GitBook: [master] 5 pages modified
2019-07-09 GitBook: [master] 9 pages modified
2019-07-10 GitBook: [master] 7 pages modified
2019-08-05 Rename scc_release_v2_3.brd.URL to scc_release_v2_3.brd
2019-08-05 Create Board_design
2019-08-05 Rename Board_design to Board_design.md
2019-08-05 Rename Board_design.md to Image_Board_design.md
2019-08-05 Rename Image_Board_design.md to Image_board_design.md
2019-08-05 Rename Schematic.md to Image_schematic.md
2019-08-20 Rename README.md to README
2019-08-20 Rename README to README.md
2019-08-21 Rename Getting_started.md to README.md
2019-08-21 Rename Getting_started.md to Getting_started(+how_to_program).md
2019-08-21 Rename readme.txt to README.md
2019-08-23 Rename SolderingBasics.md to SolderingBasics.txt
2019-08-23 Rename SolderingBasics.txt to SolderingBasics.md
2019-08-23 Create Developmental_Files
2019-08-23 Delete Developmental_Files
    Attempted at making a folder that would hold all developmental files.
2019-08-23 Create Developmental_Folder
2019-08-23 Delete Hot_Glue_Camera.jpg
    Updated the picture to outline the flex wires with purple boxes.
2019-08-23 Delete Hot_Glue_Camera.jpg
    uploaded into the wrong location

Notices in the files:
parts and their libraries:
SparkFun-Connectors: Licensing: Creative Commons ShareAlike 4.0 International - https://creativecommons.org/licenses/by-sa/4.0
